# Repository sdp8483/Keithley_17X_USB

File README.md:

# Keithley 17x USB Adapter
The following device is used to connect the Keithley 177 and 179 digital multimeter to the PC. The USB Adapter is a serial COM port enabling the user to use simple serial terminal programs to read data from the Keithley multimeter. The device fully isolates the PC from the multimeter through optoisolators and has no impact on the meters performance. The Keithley 17x USB Adapter is a simple device for connecting two great multimeters to the PC to further increase their value to hobbyists by enabling data logging.

 Top View | Bottom View   
----|-----    
 | 

The Keithley 177 and 179 Digital Multimeter have a GPIB option. If your meter has this option installed you may want to get a GPIB to USB adapter and use that. If your meter does not have this option installed then the Keithley 17x USB Adapter is for you. The original GPIB option was a daughter board that connected to the meter's main board using connector J1008. This connector is a 14 pin DIP socket located right behind the input terminals of the meter. Before continuing with the project I suggest you open up your meter and locate this connector. Below are pictures of the socket location on the three meters I have. If the socket is not soldered in but the footprint is on the PCB then don't worry. Get a suitable DIP socket and solder it in.

 Keithley 177 J1008 Location                                 | Keithley 179 J1008 Location
-------------------------------------------------------------|-------------------
| 

# Building the PCB

1. Download the [GERBER](pcb/gerber) files and order from your favorite prototype PCB board house. The PCB is double sided and is 70.5mm x 40mm in size.

2. For reflow soldering I strongly suggest getting a solder paste stencil from your prototype PCB manufacture. If ordering thorough a board house that does not offer stencils then [OSH Stencils](https://www.oshstencils.com/#%20) is a low cost option. The polyimide film 3mil stencil is more then durable enough for a few boards and the cost is just about right. For hand soldering the solder paste stencil can be omitted.

3. Order the components listed in the [BOM](pcb/bom/Keithley_17x_USB_BOM.csv). All items were ordered from [DigiKey](https://www.digikey.com/) or [LCSC](https://lcsc.com/) but it is possible to source from other suppliers.

4. Use the [Interactive BOM](pcb/bom/ibom.html) for part placement during PCB assembly.

# Programing the MSP430FR2110
1. The lowest cost solution to obtain a programmer for the MSP430 is to buy a TI Launchpad. The [MSP-EXP430FR2433](http://www.ti.com/tool/MSP-EXP430FR2433) Launchpad is a good option but any TI Lauchpad that has an onboard eZ-FET debug probe will work.

2. There are at least two software paths for uploading the firmware
    1. **TI UniFlash:** You can either install [UniFlash](http://www.ti.com/tool/UNIFLASH) or use the [UniFlash cloud tool](https://dev.ti.com/). The compiled code is in [firmware/releases](firmware/releases).

    2. **TI Code Composer Studio:** Install the latest version of [Code Composer Studio](http://www.ti.com/tool/CCSTUDIO), import the CCS project found in [firmware/keithley_17X_USB](firmware/keithley_17X_USB), and build the firmware yourself. There is also a [cloud version of CCS](https://dev.ti.com/) that you can use if you do not want to install software on your PC.

3. Remove all the jumpers from the TI Launchpad used to connect the eZ-FET to the onboard target microcontroller. Connect the eZ-FET to connector J3 on the Keithley 17x USB adapter. The pinout is labeled on the silkscreen. It is not necessary to solder a header onto the PCB, I programmed all my boards using female to male Dupont wires and held them in place while uploading the code.

# Installing the USB Adapter into the Keithley Digital Multimeter

1. Print and cutout the mounting hole locating [template](enclosure/Drawings/mounting_template.pdf).

2. Open up your digital multimeter. We need to add a few holes to the rear of the top case.

3. Using a punch and the hole locating template, mark the center of the mounting hole locations and the USB cutout.

4. Drill the mounting holes using a #29 [3.45mm] drill or closest metric size. Enjoy that old plastic smell coming from the fresh drilled hole.

5. I recommend pilot drilling the USB hole first, you can use the same size drill bit from the previous step. Then drill the USB cutout to 5/8" [15.875mm] or the closest metric size. I used a set of step drills so that the hole was gradually increased.

6. Don't forget to deburr the drilled holes.

7. Print off a [face plate](encloser/USB_face_plate.stl) so we can hide the gap around the circular cutout for the USB connector. Print at 0.2mm layer height. It's very thin so it should print fast, about 5 minutes on my Prusa clone. If you don't mind the gap you can skip this.

8. Place the top of the case to the right of the bottom of the multimeter.

9. Install the DIP connector into the DIP socket on the multimeter main board. It's hard to see it in the photo but the DIP socket has a chamfered corner on the inside pocket to indicate pin 1. Align pin 1 of the DIP socket to pin 1 of the ribbon cable, the red stripe. Don't go by the pictures below, it seems that the placement of Pin 1 on this DIP socket is different not only between the 177 and 179 but also between the same model number.

The DIP socket on my 177 was to close to the mounting pillar and required me to shave off the corner of the DIP connector.

10. Install the IDC connector on the ribbon cable. Pin 1 of the connector is indicated by a small triangle, make sure this aligns with the red stripe of the ribbon cable. Before fully attaching the IDC connector it is good to check the cable length by putting the top of the case onto the multimeter.

11. Trim the ribbon cable. A hobby knife or similar tool works.

12. Reassemble the multimeter and test it out using a serial terminal program on your PC.

# PC Connection

The Keithley 17x USB Adapter uses a FTDI serial to USB converter IC. Most operating systems should come with drivers already installed. If your system does not come with FTDI drivers you will need to download and install them from [FTDI](https://www.ftdichip.com/FTDrivers.htm).

Connect to the Keithley 17x USB Adapter using any serial terminal program such as [PuTTY](https://www.putty.org/) (Windows) or [Minicom](https://en.wikipedia.org/wiki/Minicom) (Linux).  You can also use the Arduino serial monitor. The Keithley 17x USB Adapter is setup for a baud rate of 115200 8N1.

# Python GUI

If you have Python 3.x installed on your computer you can also use the [Python GUI](software/17X_UART_Receiver). Run the GUI from a terminal using the following command: `python Keithley_17X_USB/software/17X_UART_Reciever/main.py`
 
Select the model of multimeter you are connecting to. A window will popup that will let you select the serial port of the multimeter you want to connect. After connecting select the measurement units and the measurement range of the meter. The range switches on the GUI **do not** change the range on the multimeter, they simply format the GUI display to match the multimeter display. There is no way for the USB Adapter to change the range on the multimeter, it is a read only device.

# Theory of Operation

Below is a screenshot from the display section of the schematic for the Keithley 177, the 179 display is similar. Connector J1008 is on the right of the schematic. This connects to the data bus between the main multimeter IC U106 and the display. The USB adapter taps into this data bus to decode the data being sent to the display. 

The `D5` signal is high when the fifth digit on the display is on, the fifth digit is the left most digit when looking at the display. This signal is high for 2ms. `B1`, `B2`, `B4`, and `B8` are the four bit value that this display is showing. In the logic analyzer capture below only `B1` is high therefor digit 5 is `1`. Since the other digits are not available on this data bus the USB Adapter hardware triggers off a rising `D5` signal and then uses hardware timers to sample the remaining digits which are all 2ms in length. The above example decodes to `19089`. Notice how there is no signal for the decimal place on the data bus available to the USB adapter. Since the `sign` signal is high that means that the value displayed is positive. The `overange` signal will strobe high and then low signaling that the meter is out of its measurement range, this signal was not outside of the range since I was connected to a 1.9000V reference and the meter was in its 2V range.

S

What about `Clock`? The clock signal is ignored by the USB adapter since it was not consistent across the two meter models that this project was targeting. You may notice that JP1 of the USB Adapter seems like it was put there as a way to select the conversion trigger off of the `D5` or `Clock` signal. You are not wrong, that was my original intent but I found it was easier to only trigger off of `D5`.

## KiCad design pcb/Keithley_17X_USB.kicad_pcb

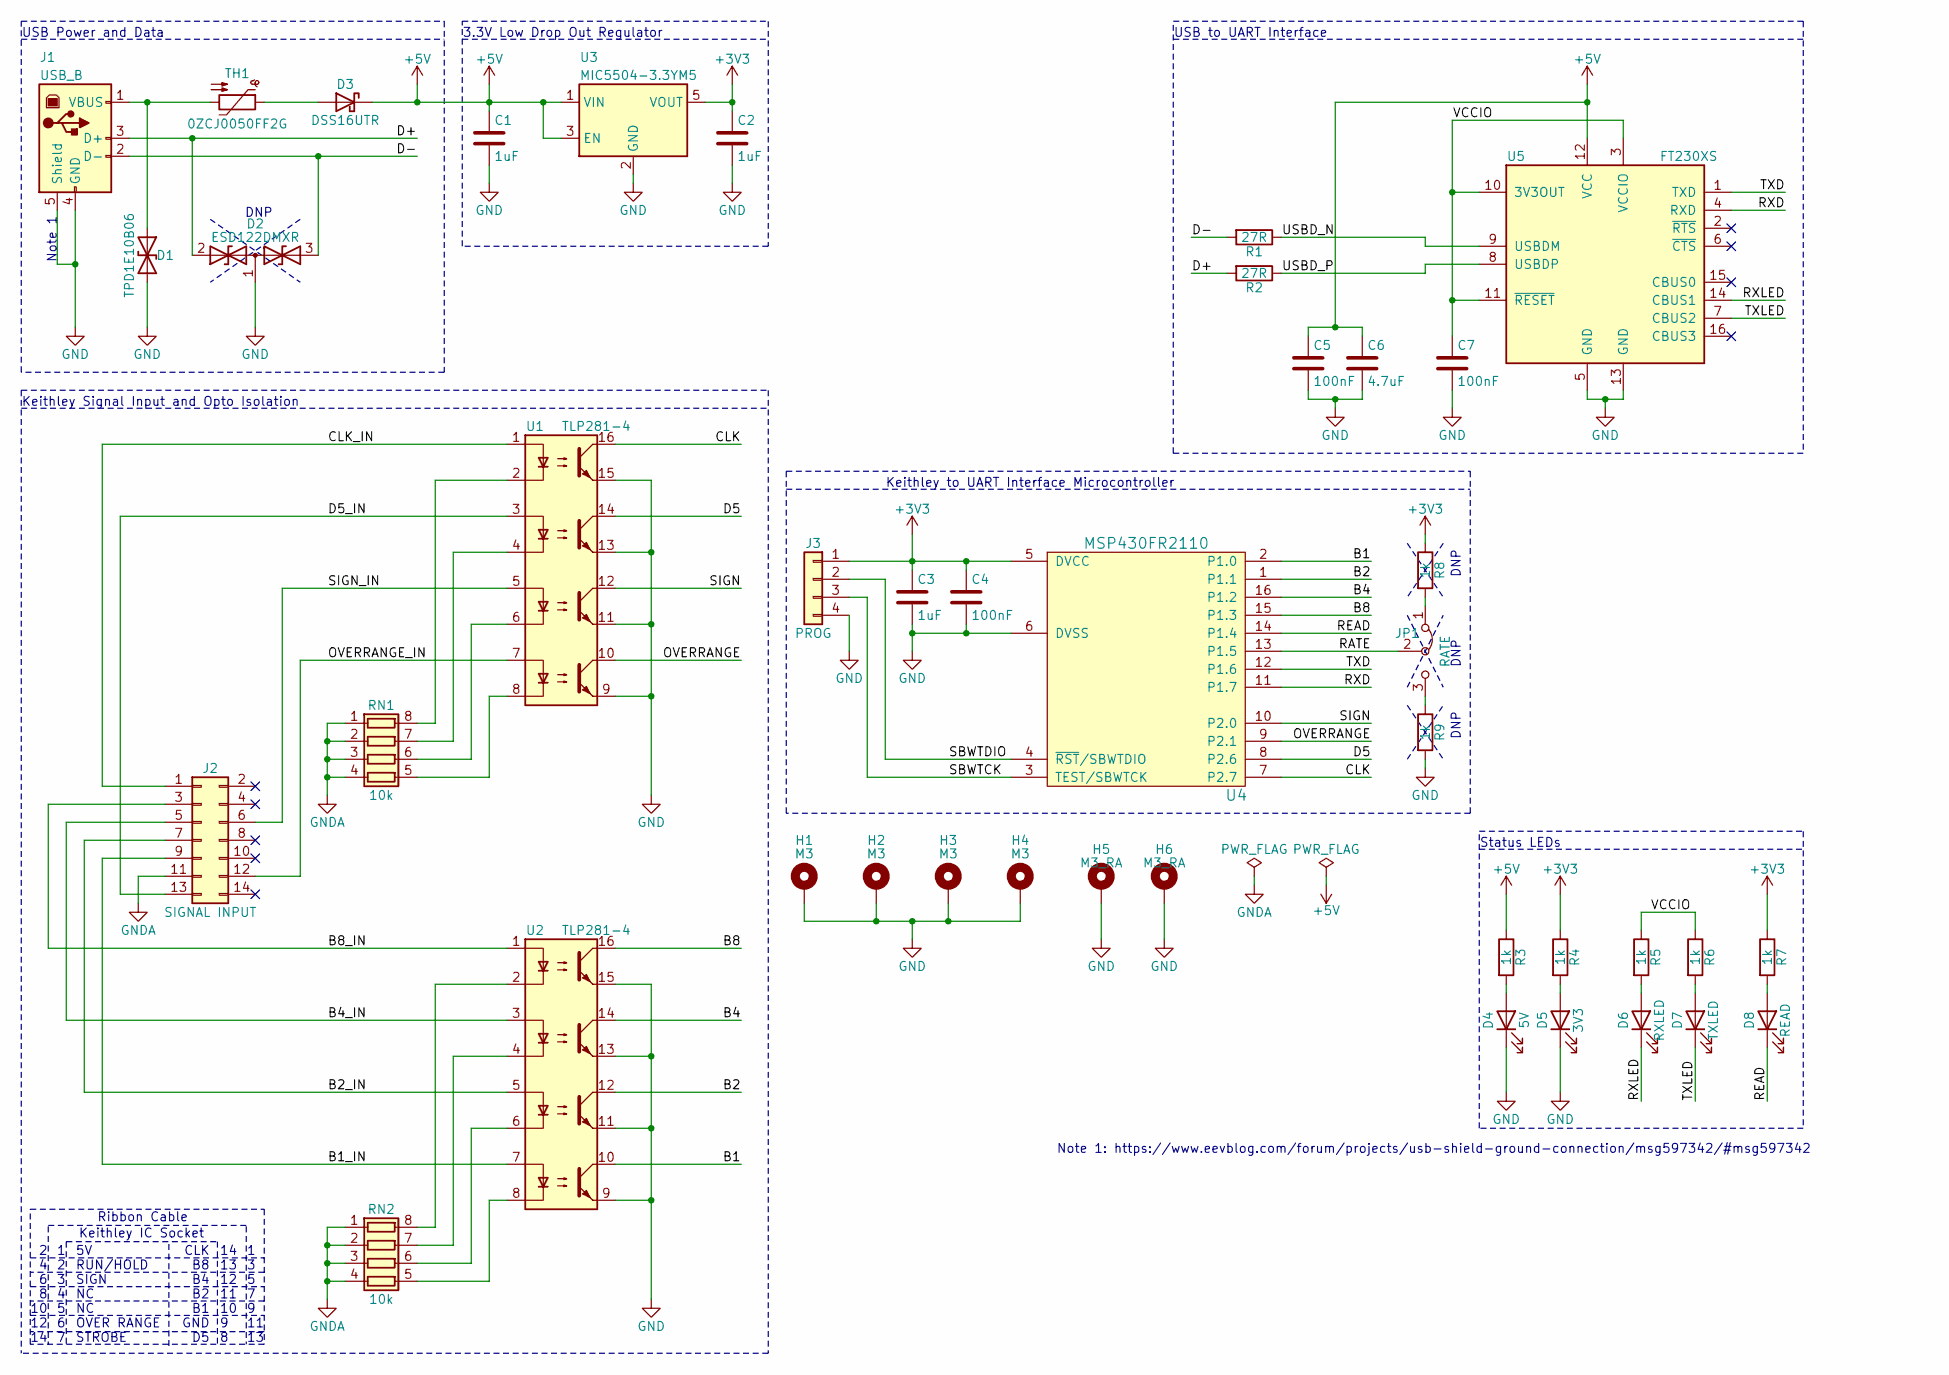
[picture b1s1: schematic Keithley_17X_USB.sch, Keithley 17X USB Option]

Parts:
C1, C2, C3: 1uF; C_0603_1608Metric; Mfg Part Number CL10A105KQ8NNNC
C4, C5, C7: 100nF; C_0603_1608Metric; Mfg Part Number C0603C104Z3VACTU
C6: 4.7uF; C_0603_1608Metric; Mfg Part Number CL10A475KQ8NNNC
D1: TPD1E10B06; TI_PX1SON_DPY; Mfg Part Number TPD1E10B06QDPYRQ1
D2: ESD122DMXR; TI_DMX_X2SON; Mfg Part Number ESD122DMXR
D3: DSS16UTR; D_SOD-123FL; Mfg Part Number DSS16UTR
D4: 5V; LED_0805_2012Metric; Mfg Part Number NCD0805R1
D5: 3V3; LED_0805_2012Metric; Mfg Part Number NCD0805R1
D6: RXLED; LED_0805_2012Metric; Mfg Part Number NCD0805R1
D7: TXLED; LED_0805_2012Metric; Mfg Part Number NCD0805R1
D8: READ; LED_0805_2012Metric; Mfg Part Number NCD0805R1
H1, H2, H3, H4: M3; MountingHole_3.2mm_M3_DIN965_Pad
H5, H6: M3_RA; Keystone_Screw-Terminal_7761_RightAngle; Mfg Part Number 7761
J1: USB_B; USB_B_OST_USB-B1HSxx_Horizontal; Mfg Part Number E8144-B02022-L
J2: SIGNAL INPUT; PinHeader_2x07_P2.54mm_Horizontal; Mfg Part Number 302-R141
J3: PROG; PinHeader_1x04_P2.54mm_Vertical
JP1: RATE; PinHeader_1x03_P2.54mm_Vertical
R1, R2: 27R; R_0603_1608Metric; Mfg Part Number RMCF0603JT27R0
R3, R4, R5, R6, R7, R8, R9: 1k; R_0603_1608Metric; Mfg Part Number RC0603JR-071KL
RN1, RN2: 10k; YC324-JK-0710KL; Mfg Part Number YC324-JK-0710KL
TH1: 0ZCJ0050FF2G; Fuse_1206_3216Metric; Mfg Part Number 0ZCJ0050FF2G
U1, U2: TLP281-4; SOIC-16_4.55x10.3mm_P1.27mm; Mfg Part Number TLP281-4(GB-TP,J,F
U3: MIC5504-3.3YM5; SOT-23-5; Mfg Part Number MIC5504-3.3YM5-TR
U4: MSP430FR2110; TSSOP-16_4.4x5mm_P0.65mm; Mfg Part Number MSP430FR2110IPW16R
U5: FT230XS; SSOP-16_3.9x4.9mm_P0.635mm; Mfg Part Number FT230XS-R

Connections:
+3V3: C2.1, C3.1, C4.1, J3.1, R4.1, R7.1, R8.1, U3.5 (VOUT), U4.5 (DVCC)
+5V: C1.1, C5.1, C6.1, D3.1 (K), R3.1, U3.1 (VIN), U3.3 (EN), U5.12 (VCC)
/B1: U2.10, U4.2 (P1.0)
/B1_IN: J2.9, U2.7
/B2: U2.12, U4.1 (P1.1)
/B2_IN: J2.7, U2.5
/B4: U2.14, U4.16 (P1.2)
/B4_IN: J2.5, U2.3
/B8: U2.16, U4.15 (P1.3)
/B8_IN: J2.3, U2.1
/CLK: U1.16, U4.7 (P2.7)
/CLK_IN: J2.1, U1.1
/D5: U1.14, U4.8 (P2.6)
/D5_IN: J2.13, U1.3
/D+: D2.2 (A1), J1.3 (D+), R2.2
/D-: D2.3 (A2), J1.2 (D-), R1.2
/OVERRANGE: U1.10, U4.9 (P2.1)
/OVERRANGE_IN: J2.12, U1.7
/RATE: JP1.2 (C), U4.13 (P1.5)
/READ: D8.1 (K), U4.14 (P1.4)
/RXD: U4.11 (P1.7), U5.4 (RXD)
/RXLED: D6.1 (K), U5.14 (CBUS1)
/SBWTCK: J3.3, U4.3 (TEST/SBWTCK)
/SBWTDIO: J3.2, U4.4 (~RST~/SBWTDIO)
/SIGN: U1.12, U4.10 (P2.0)
/SIGN_IN: J2.6, U1.5
/TXD: U4.12 (P1.6), U5.1 (TXD)
/TXLED: D7.1 (K), U5.7 (CBUS2)
/USBD_N: R1.1, U5.9 (USBDM)
/USBD_P: R2.1, U5.8 (USBDP)
/VCCIO: C7.1, R5.1, R6.1, U5.3 (VCCIO), U5.10 (3V3OUT), U5.11 (~RESET)
GND: C1.2, C2.2, C3.2, C4.2, C5.2, C6.2, C7.2, D1.2 (A2), D2.1 (common), D4.1 (K), D5.1 (K), H1.1, H2.1, H3.1, H4.1, H5.1, H6.1, J1.4 (GND), J1.5 (Shield), J3.4, R9.2, U1.9, U1.11, U1.13, U1.15, U2.9, U2.11, U2.13, U2.15, U3.2 (GND), U4.6 (DVSS), U5.5 (GND), U5.13 (GND)
GNDA: J2.11, RN1.1 (R1.1), RN1.2 (R2.1), RN1.3 (R3.1), RN1.4 (R4.1), RN2.1 (R1.1), RN2.2 (R2.1), RN2.3 (R3.1), RN2.4 (R4.1)
unnamed: D1.1 (A1), J1.1 (VBUS), TH1.2
unnamed: D3.2 (A), TH1.1
unnamed: D4.2 (A), R3.2
unnamed: D5.2 (A), R4.2
unnamed: D6.2 (A), R5.2
unnamed: D7.2 (A), R6.2
unnamed: D8.2 (A), R7.2
unnamed: JP1.1 (A), R8.2
unnamed: JP1.3 (B), R9.1
unnamed: RN1.5 (R4.2), U1.8
unnamed: RN1.6 (R3.2), U1.6
unnamed: RN1.7 (R2.2), U1.4
unnamed: RN1.8 (R1.2), U1.2
unnamed: RN2.5 (R4.2), U2.8
unnamed: RN2.6 (R3.2), U2.6
unnamed: RN2.7 (R2.2), U2.4
unnamed: RN2.8 (R1.2), U2.2

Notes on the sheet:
USB Power and Data
USB to UART Interface
Keithley to UART Interface Microcontroller
3.3V Low Drop Out Regulator
Keithley Signal Input and Opto Isolation
Status LEDs
5V RUN/HOLD SIGN NC NC OVER RANGE STROBE
CLK B8 B4 B2 B1 GND D5
1 2 3 4 5 6 7
14 13 12 11 10 9 8
2 4 6 8 10 12 14
1 3 5 7 9 11 13
Keithley IC Socket
Ribbon Cable
Note 1
Note 1: https://www.eevblog.com/forum/projects/usb-shield-ground-connection/msg597342/#msg597342
DNP

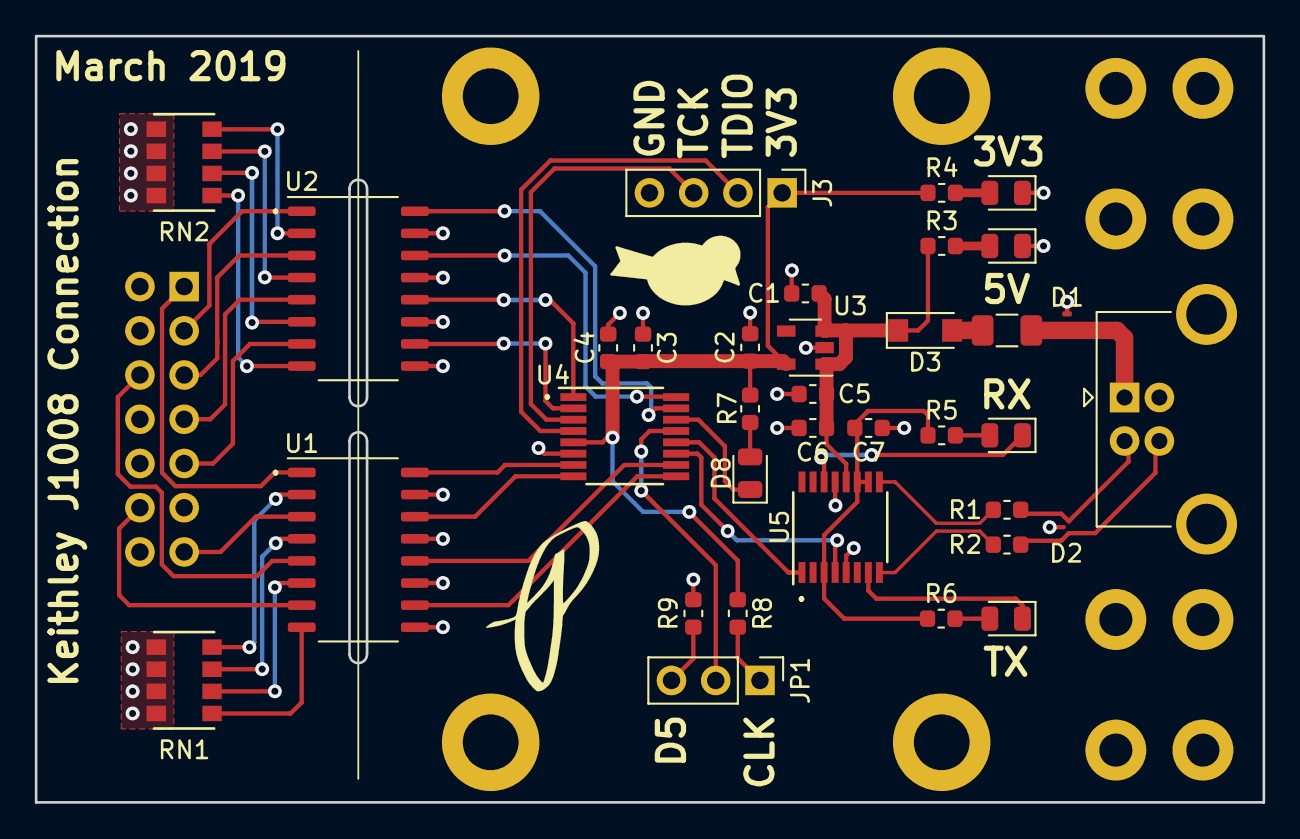
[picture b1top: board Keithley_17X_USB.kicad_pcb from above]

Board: 2 copper layers, 70.5 x 44.0 mm, 42 parts (1 on the bottom side), 50 nets.

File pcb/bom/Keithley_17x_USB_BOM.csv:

References,Description,Manufacture,Mfg Part Number,Supplier,Supplier Part Number,Value,Footprint,Quantity
"C4, C5, C7",CAP CER 0.1UF 25V Y5V 0603,KEMET,C0603C104Z3VACTU,Digi-Key,399-1100-1-ND,100nF,C_0603_1608Metric,3
"C1, C2, C3",CAP CER 1UF 6.3V X5R 0603,Samsung Electro-Mechanics,CL10A105KQ8NNNC,Digi-Key,1276-1036-1-ND,1uF,C_0603_1608Metric,3
C6,CAP CER 4.7UF 6.3V X5R 0603,Samsung Electro-Mechanics,CL10A475KQ8NNNC,Digi-Key,1276-1045-1-ND,4.7uF,C_0603_1608Metric,1
"R1, R2",RES 27 OHM 5% 1/10W 0603,Stackpole Electronics Inc,RMCF0603JT27R0,Digi-Key,RMCF0603JT27R0CT-ND,27R,R_0603_1608Metric,2
"R3, R4, R5, R6, R7, R8, R9",RES SMD 1K OHM 5% 1/10W 0603,Yageo,RC0603JR-071KL,Digi-Key,311-1.0KGRCT-ND,1k,R_0603_1608Metric,7
"D4, D5, D6, D7, D8",Red 615~630nm 0805 Light Emitting Diodes (LED) RoHS,Foshan NationStar Optoelectronics,NCD0805R1,LCSC,C84256,"5V, 3V3, RXLED, TXLED, READ",LED_0805_2012Metric,5
D3,SCHOTTKY 60V SOD-123FL,SMC Diode Solutions,DSS16UTR,Digi-Key,1655-1929-1-ND,DSS16UTR,D_SOD-123FL,1
D1,TVS DIODE 5.5V 14V 2X1SON,Texas Instruments,TPD1E10B06QDPYRQ1,Digi-Key,296-45327-1-ND,TPD1E10B06,TI_PX1SON_DPY,1
D2,TVS DIODE 8.4VC 2.5A IPP 3X2SON,Texas Instruments,ESD122DMXR,Digi-Key,296-48543-1-ND,ESD122DMXR,TI_DMX_X2SON,1
U4,IC MCU 16BIT 2KB FRAM 16TSSOP,Texas Instruments,MSP430FR2110IPW16R,Digi-Key,296-47343-1-ND,MSP430FR2110,TSSOP-16_4.4x5mm_P0.65mm,1
U3,IC REG LINEAR 3.3V 300MA SOT23-5,Microchip Technology,MIC5504-3.3YM5-TR,Digi-Key,576-4764-1-ND,MIC5504-3.3YM5,SOT-23-5,1
U5,IC USB SERIAL BASIC UART 16SSOP,"FTDI, Future Technology Devices International Ltd",FT230XS-R,Digi-Key,768-1135-1-ND,FT230XS,SSOP-16_3.9x4.9mm_P0.635mm,1
"U1, U2",OPTOISO 2.5KV 4CH TRANS 16-SOP,Toshiba Semiconductor and Storage,"TLP281-4(GB-TP,J,F",,,TLP281-4,SOIC-16_4.55x10.3mm_P1.27mm,2
TH1,PTC RESET FUSE 8V 500MA 1206,Bel Fuse Inc.,0ZCJ0050FF2G,Digi-Key,507-1802-1-ND,0ZCJ0050FF2G,Fuse_1206_3216Metric,1
"RN1, RN2",RES ARRAY 4 RES 10K OHM 2012,Yageo,YC324-JK-0710KL,Digi-Key,YC324J-10KCT-ND,10k,YC324-JK-0710KL,2
"H5, H6",TERM SCREW M3 4 PIN PCB RA,Keystone Electronics,7761,Digi-Key,36-7761-ND,M3_RA,Keystone_Screw-Terminal_7761_RightAngle,2
J1,CONN RCPT TYPEB 4POS R/A,Pulse Electronics Network,E8144-B02022-L,Digi-Key,553-2272-ND,USB_B,USB_B_OST_USB-B1HSxx_Horizontal,1
J2,CONN HEADER R/A 14POS 2.54MM,On Shore Technology Inc.,302-R141,Digi-Key,ED10534-ND,SIGNAL INPUT,PinHeader_2x07_P2.54mm_Horizontal,1
,DIP CABLE - HDP14S/AE14G/X ,Assmann WSW Components,H2PXS-1418G,Digi-Key,H2PXS-1418G-ND,,,1
,IDCconnector 14,Ckmtw(Shenzhen Cankemeng),C146586,LCSC,C146586,,,1

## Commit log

2019-02-10 init commit
2019-02-10 ignore more
2019-02-10 remove lnk_msp430fr2000.cmd
2019-02-10 create file
2019-02-10 renamed to uart.h
2019-02-10 update with funcitons
2019-02-10 start schematic
2019-02-11 custom symbol from standard lib
2019-02-11 add ldo symbol
2019-02-11 added more stuff!
2019-02-14 add ESD info
2019-02-14 clean up schematic, final or darn close
2019-02-15 add component feild values
2019-02-15 change GPIO to bidirectional to make erc happy
2019-02-15 annotate
2019-02-16 create PX1SON 3d model
2019-02-16 create XSON 3d model
2019-02-16 create custom footprint
2019-02-16 update with footprints
2019-02-18 add more footprints and 3d models
2019-02-18 add r_array footprint and 3d model
2019-02-18 add right angle mounting holes
2019-02-18 save changes
2019-02-19 create 3d model
2019-02-19 add right angle mount
2019-02-20 added rate selection, trigger on clk or D5. Future implementation
2019-02-20 change TH1 name to part number
2019-02-23 add usb connector 3d model
2019-02-24 add missing 3d models
2019-02-24 rearaned B1 B2 B4 and B8 connection to opto for better layout
2019-02-24 update 3d model to shrouded header
2019-02-24 update with proper colors
2019-02-24 lable right side of usb data lines for differential pair routing
2019-02-24 connect usb sheild to ground
2019-02-24 ground right angle mounts
2019-02-24 rename usb differential pairs to what kicad expects
2019-02-24 label VCCIO net
2019-02-24 rx/tx leds powered using vccio
2019-02-26 shrink length by 15mm
2019-02-26 rearange Port 2 connections to simplfy layout
2019-03-01 draft layout, need to cleanup and make pretty
2019-03-04 ignore osx files
2019-03-10 remove reference to missing fuse 3d model
2019-03-10 added small flat on side for assembly
2019-03-10 update silkscreen
2019-03-19 generate BOM
2019-03-19 minor silkscreen cleanup
2019-03-19 update with bluebird logo
2019-03-19 add bluebird logo
2019-03-19 output gerber files
2019-03-19 reduce flood fill outside board outline
2019-03-23 add vertical center line
2019-03-23 remove
2019-03-24 shift z-axis zero to bottom of part
2019-03-24 adjust stock for 1mm below z-axis for cleanup
2019-03-24 output gcode
2019-03-24 moved enclosure CAD files to descriptive directory
2019-03-24 split CAD models so that assembly workbench is happy
    Assembly 2 is unable to use files with CAM featrues, sees as multiple models and complains
2019-03-24 add to and bottom
2019-03-24 move and rename instruemtn case model
2019-03-24 modify with mounting holes for USB
2019-03-24 add instument case, calibration, and face plate
2019-03-24 create CAM files
2019-03-24 update with new faceplate thicnkess
2019-03-24 add viewign window to instument case to see inside
2019-03-30 add detailed drawing
2019-03-30 export drawing to pdf
2019-04-06 not CNC machining faceplate
2019-04-06 add CAM to file name
2019-04-06 add 2d drawings of enclosure and face plate
2019-04-06 update pocket cutout type to zigzagOffset. Set new tool info
2019-04-07 generate interactive bom
2019-04-07 change interrupt trigger from CLK to D5
2019-04-07 target MSP430FR2110
2019-04-07 trigger on D5 requires high to low transistion
2019-04-08 pull P1.4 low to turn on, logic was inversed
2019-04-14 added drawing
2019-04-17 cleanup, new TI compiler
2019-04-17 DNP R8, R9, and JP1
2019-04-21 reduced step depth to 0.06inch
2019-04-21 reduce feeds to 1.5mm/s
2019-10-26 move pcb files to dir
2019-11-18 update ibom
2019-11-18 remove componets from ibom
2019-11-18 remove TVS from ibom
2019-11-18 update ccs project
2019-11-19 copy example python serial GUI code
2019-11-21 ignore .pyc
2019-11-22 add radio buttons for units, not working yet
2019-11-22 ignore .vscode settings
2019-11-22 ignore vscode settings
2019-11-22 .gitignore fix
2019-11-22 ignore pyinstaller build directories
2019-11-22 ignore pyinstaller .spec files
2019-11-24 main.py lauches individual guis for each keithley model
2019-11-24 reduce width
2019-11-24 change layout
2019-11-25 rename to keithley.py
2019-11-25 add multi model number feature
2019-11-25 add multiple model buttons
2019-11-25 write ini file with last used switch position
2019-11-25 generate ini file for each gui
2019-11-25 add semi useful comments
2019-11-25 no more examples
2019-12-13 clean up
2020-05-13 create drill template
2020-05-15 remove redundant constraints
2020-05-15 increase USB cuttout size
2020-05-15 move to FreeCAD dir
2020-05-15 add files for 3d printing
2020-05-15 DNP D2
2020-05-15 generate pdf of schema
2020-05-16 generate new iBOM
2020-05-16 add LEDs part number
2020-05-16 update netlist
2020-05-16 read updated netlist
2020-05-16 Update Keithley_17X_USB.sch-bak
2020-05-16 start adding details
2020-05-16 fix some grammer errors
2020-05-17 update drill template
2020-05-17 add installation instructions
2020-05-17 add PC conneciton section
2020-05-25 clean up wording
2020-05-25 no dummy
2020-05-25 start theory of operation
2020-05-26 small wording fix
2020-05-26 make command path clear
2020-05-27 add logic analizer capture
2020-05-27 finish theory section
2020-05-27 dont ignore csv files
2020-05-27 fix numbering

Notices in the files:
parts and their libraries:
Copyright 2016 Accelerated Designs. All rights reserved.
